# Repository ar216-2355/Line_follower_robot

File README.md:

ライントレーサー用基板

- ESP-WROOM-02搭載可能
- LCD搭載可能
- MPU6050搭載可能　->　倒立振子にもなる

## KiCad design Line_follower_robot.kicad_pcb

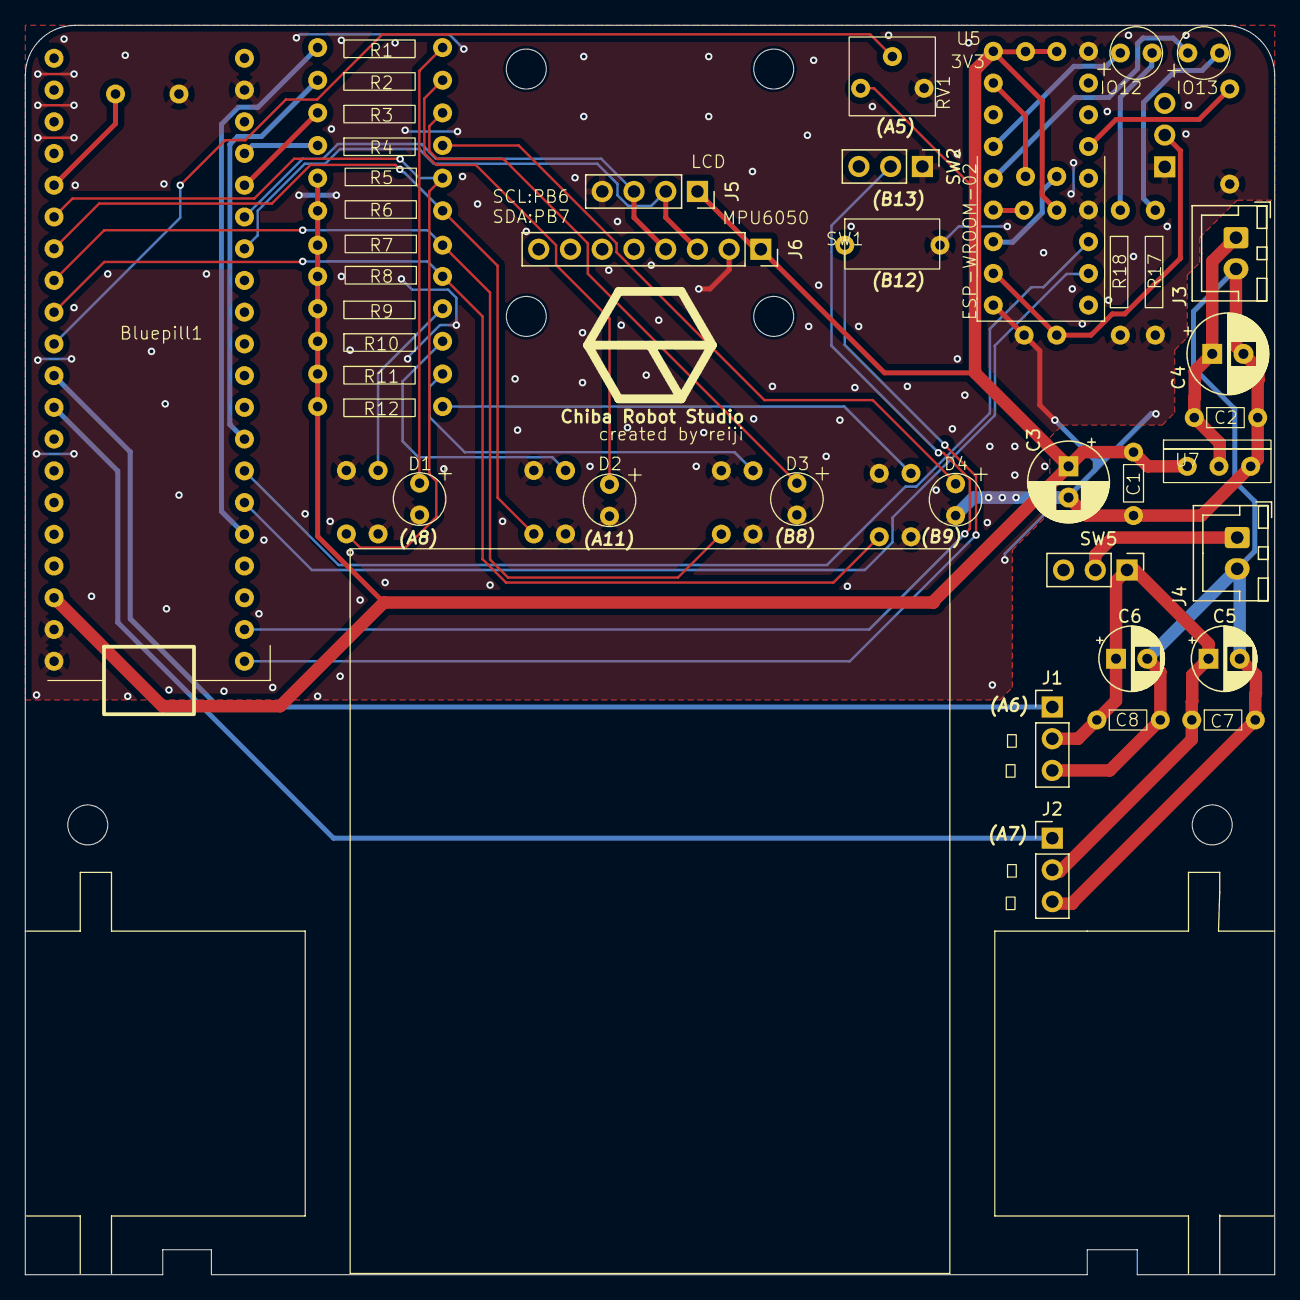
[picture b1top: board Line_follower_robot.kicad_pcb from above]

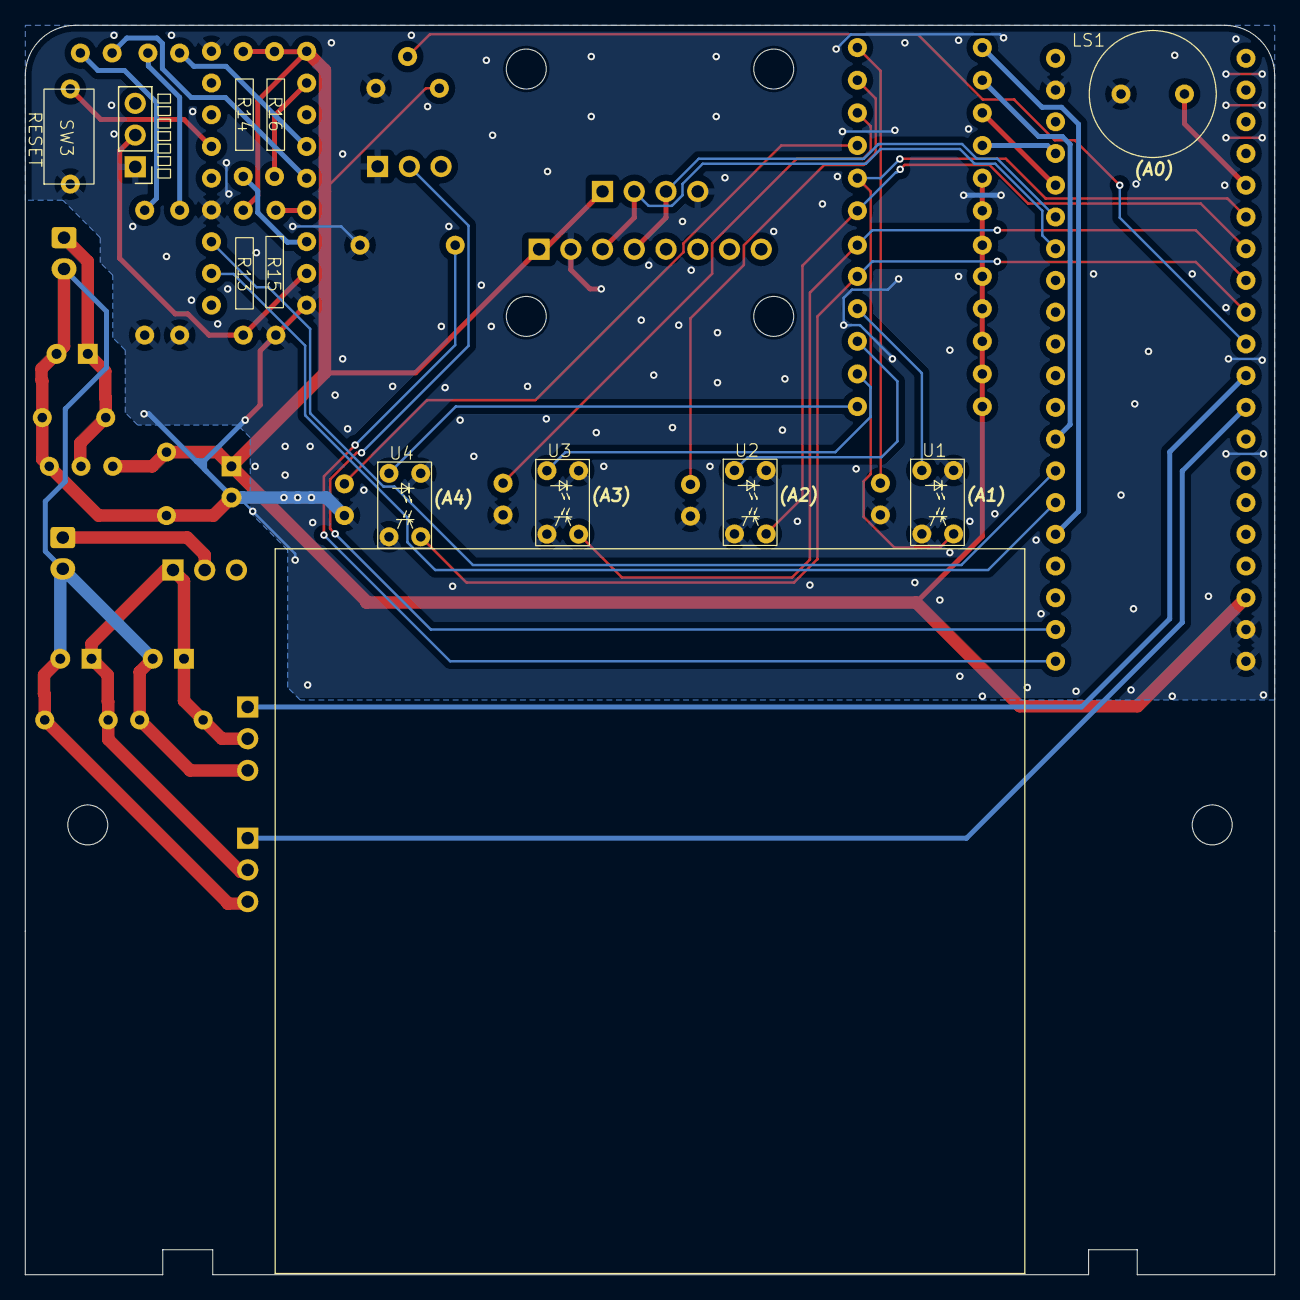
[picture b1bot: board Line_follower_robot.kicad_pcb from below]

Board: 2 copper layers, 100.0 x 100.0 mm, 52 parts (11 on the bottom side), 40 nets.

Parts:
Bluepill1: blue pill
C1, C2, C7, C8: 0.1u; capa_5.1
C3, C4: 10u; CP_Radial_D6.3mm_P2.50mm
C5, C6: 100u; CP_Radial_D5.0mm_P2.50mm
D1, D2, D3, D4: LED; LED_2.54mm
IO12, IO13: LED; LED_2.54mm
J1, J2: Conn_01x03; PinHeader_1x03_P2.54mm_Vertical
J3, J4: Conn_01x02; JST_XH_B2B-XH-A_1x02_P2.50mm_Vertical
J5: Conn_01x04_Socket; PinSocket_1x04_P2.54mm_Vertical
J6: Conn_01x08_Socket; PinSocket_1x08_P2.54mm_Vertical
LS1: Speaker; my_speaker
R1, R2, R3, R4, R17, R18: 440; resistor_10mm
R5, R6, R7, R8, R13, R14, R15, R16: 10k; resistor_10mm
R9, R10, R11, R12: 100; resistor_10mm
RV1: R_Potentiometer; Potentionmeter
SW1, SW3: SW_Push; tact_switch
SW2, SW4, SW5: SW_SPDT_321; PinHeader_1x03_P2.54mm_Vertical
U1, U2, U3, U4: BPR-105F; photo_refrector
U5: esp_wroom_02; esp32_wroom_02
U7: AZ1117-3.3; 3v3regulator

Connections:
+3.3V: Bluepill1.18 (B8), C1.1, C3.1, J5.1, J6.1, R5.2, R6.2, R7.2, R8.2, R9.1, R10.1, R11.1, R12.1, R13.2, R14.2, R16.2, RV1.2, U5.1 (3V3), U7.2 (VO)
+4V: C2.1, C4.1, J3.1, U7.3 (VI)
+6V: C5.1, C6.1, C7.1, C8.1, J1.2, J2.2, SW5.1 (C)
GND: Bluepill1.19 (B7), Bluepill1.20 (B6), Bluepill1.22 (B4), C1.2, C2.2, C3.2, C4.2, C5.2, C6.2, C7.2, C8.2, D1.2 (A), D2.2 (A), D3.2 (A), D4.2 (A), J1.3, J2.3, J3.2, J4.2, J5.4, J6.2, LS1.1, R15.2, R17.2, R18.2, RV1.1, SW1.2, SW2.1 (C), SW3.1, SW4.1 (C), U1.2 (A), U1.3 (C), U2.2 (A), U2.3 (C), U3.2 (A), U3.3 (C), U4.2 (A), U4.3 (C), U5.9 (GND), U5.10 (GND), U5.15 (GND), U7.1 (GND)
unnamed: Bluepill1.5 (A0), LS1.2
unnamed: Bluepill1.6 (A1), R5.1, U1.4 (E)
unnamed: Bluepill1.7 (A2), R6.1, U2.4 (E)
unnamed: Bluepill1.8 (A3), R7.1, U3.4 (E)
unnamed: Bluepill1.9 (A4), R8.1, U4.4 (E)
unnamed: Bluepill1.10 (A5), RV1.3
unnamed: Bluepill1.11 (A6), J1.1
unnamed: Bluepill1.12 (A7), J2.1
unnamed: Bluepill1.36 (GND), R1.1
unnamed: Bluepill1.35 (3.3V), U5.17 (RXD)
unnamed: Bluepill1.34 (RES), U5.16 (TXD)
unnamed: Bluepill1.33 (B12), R2.1
unnamed: Bluepill1.27 (A10), J5.2, J6.3
unnamed: Bluepill1.26 (A11), J5.3, J6.4
unnamed: Bluepill1.25 (A12), R3.1
unnamed: Bluepill1.24 (A15), R4.1
unnamed: Bluepill1.40, SW1.1
unnamed: Bluepill1.39, SW2.2 (B)
unnamed: D1.1 (K), R1.2
unnamed: D2.1 (K), R2.2
unnamed: D3.1 (K), R3.2
unnamed: D4.1 (K), R4.2
unnamed: IO13.1 (K), U5.5 (IO13)
unnamed: IO13.2 (A), R17.1
unnamed: IO12.1 (K), U5.4 (IO12)
unnamed: IO12.2 (A), R18.1
unnamed: J4.1, SW5.2 (B)
unnamed: R13.1, SW4.2 (B), U5.8 (IO0)
unnamed: R9.2, U1.1 (K)
unnamed: R10.2, U2.1 (K)
unnamed: R11.2, U3.1 (K)
unnamed: R12.2, U4.1 (K)
unnamed: R16.1, U5.2 (EN)
unnamed: R14.1, U5.7 (IO2)
unnamed: R15.1, U5.6 (IO15)
unnamed: SW3.2, U5.13 (RST)

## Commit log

2026-01-07 readme
2026-01-07 readme2
2026-01-07 readmw3
